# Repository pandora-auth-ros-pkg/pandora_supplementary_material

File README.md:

pandora_supplementary_material
==============================

Contains supplementary material, such as images, datasets, etc..

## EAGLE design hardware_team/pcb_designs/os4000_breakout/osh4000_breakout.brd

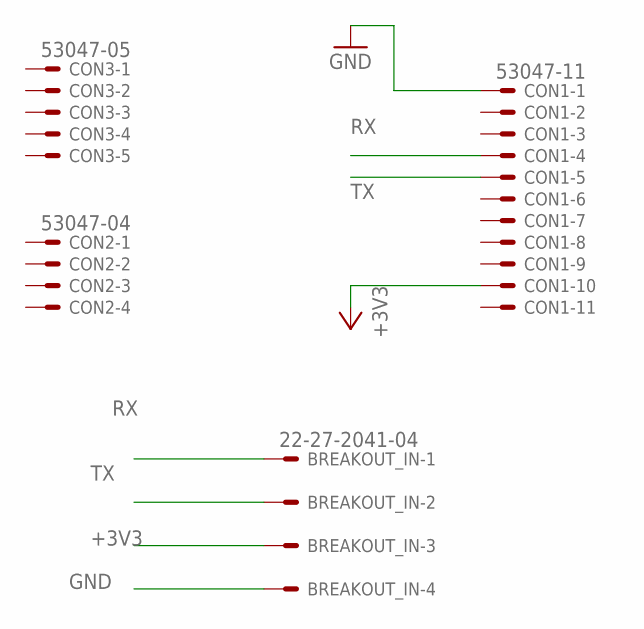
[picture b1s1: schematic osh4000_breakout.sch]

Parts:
BREAKOUT_IN: 22-27-2041-04; 6410-04
CON1: 53047-11
CON2: 53047-04
CON3: 53047-05

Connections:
+3V3: BREAKOUT_IN.3, CON1.10
GND: BREAKOUT_IN.4, CON1.1
RX: BREAKOUT_IN.1, CON1.4
TX: BREAKOUT_IN.2, CON1.5

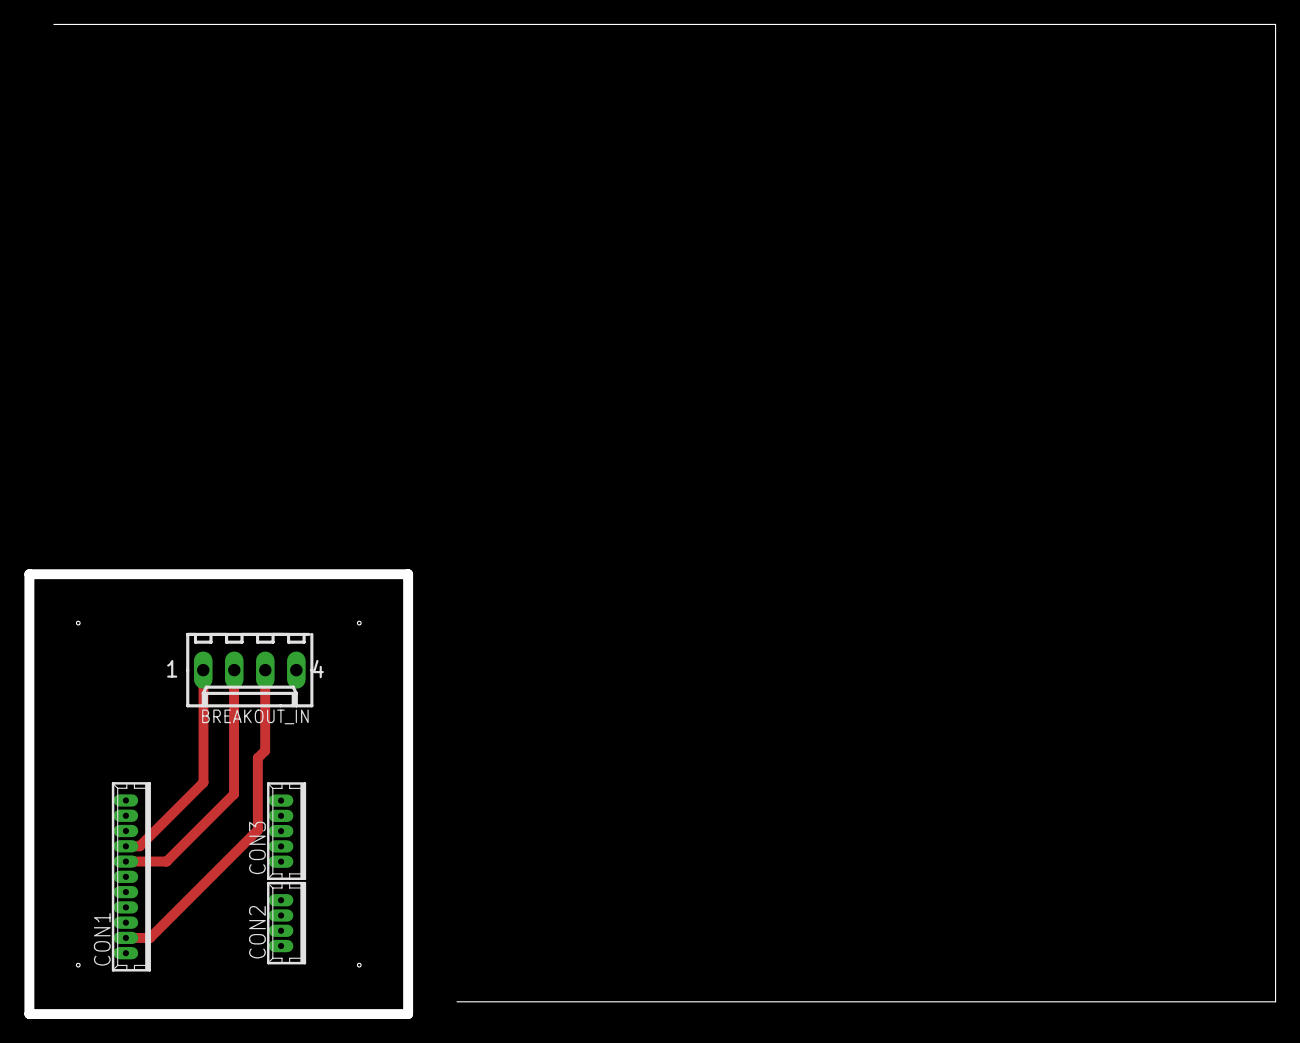
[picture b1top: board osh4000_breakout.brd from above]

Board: 2 copper layers, 31.0 x 36.0 mm, 4 parts (0 on the bottom side), 4 nets.

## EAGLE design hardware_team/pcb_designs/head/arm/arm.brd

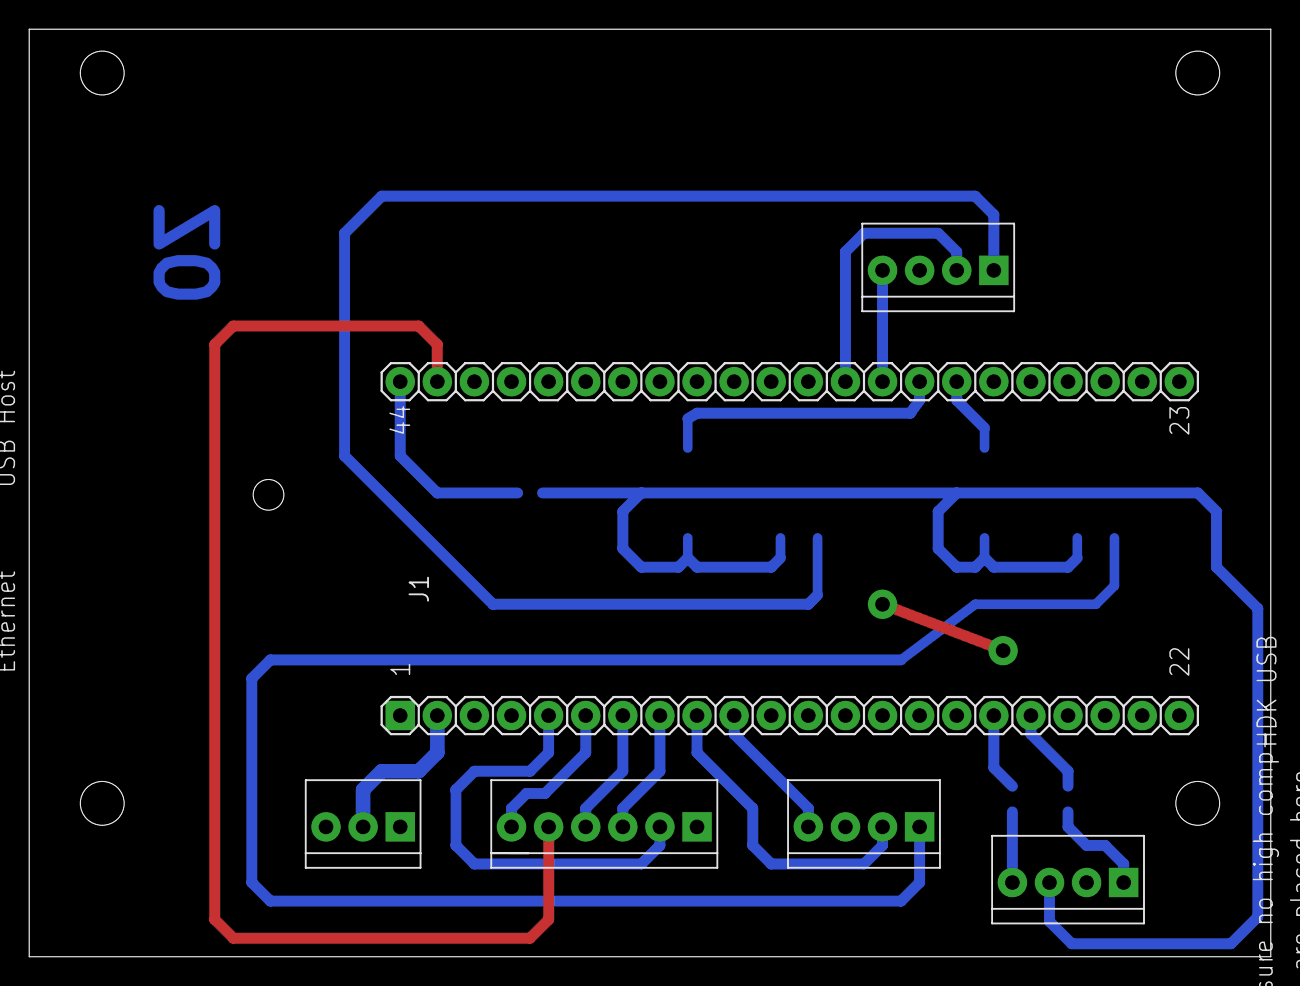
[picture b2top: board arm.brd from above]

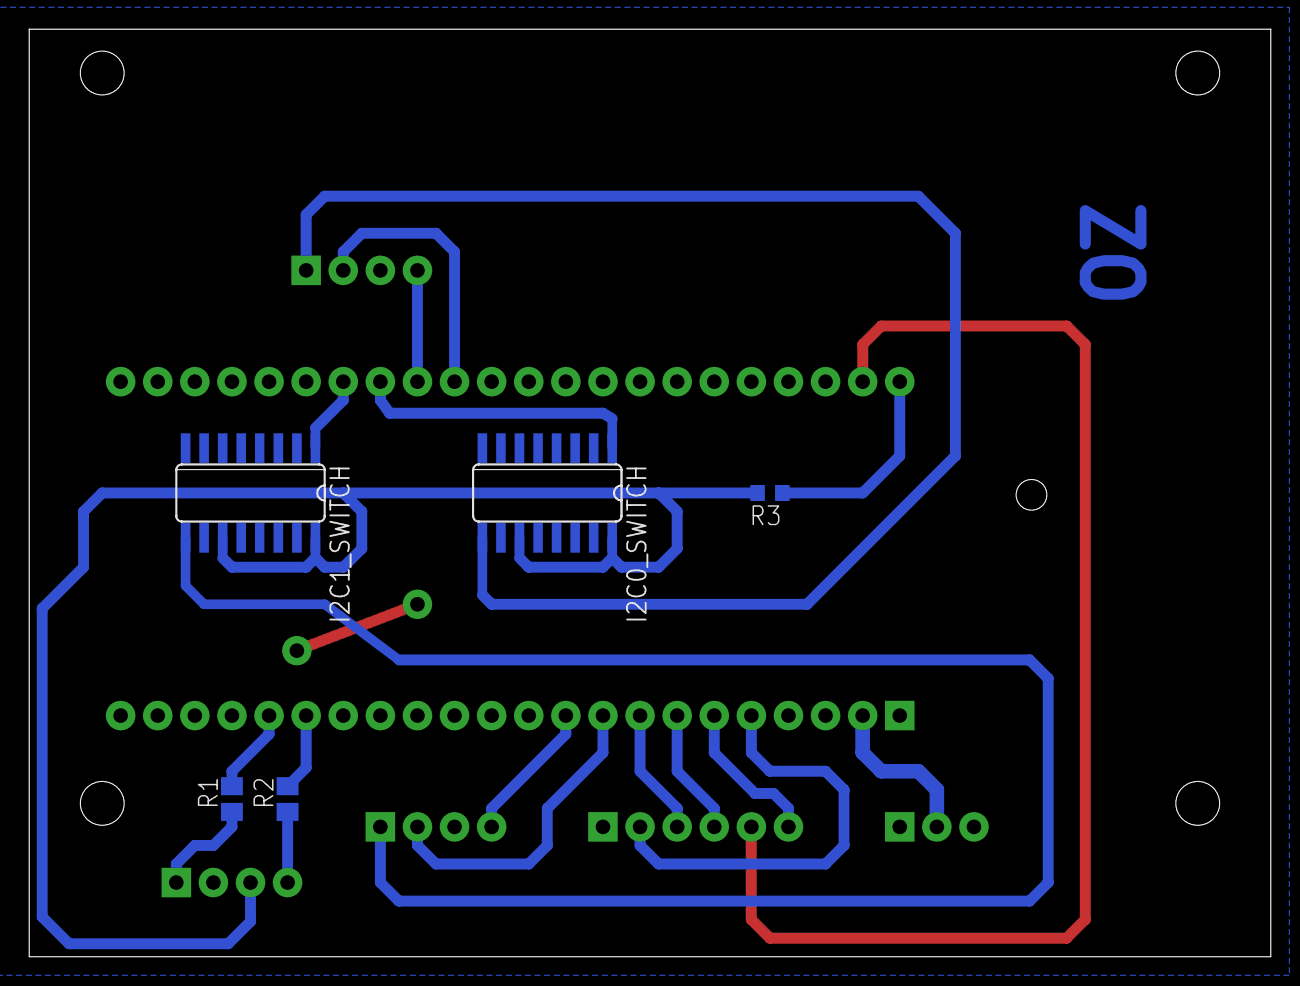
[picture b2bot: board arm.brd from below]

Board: 2 copper layers, 85.0 x 63.5 mm, 11 parts (5 on the bottom side), 21 nets.

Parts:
I2C0, I2C1: A2542WV-04P
I2C0_SWITCH, I2C1_SWITCH: MAX4674ESE+; SO16
J1: LPC4088_QUICKSTART_BOARD_REV-A
POWER: A2542WV-03P
R1, R2: 1k; R0805
R3: 1; R0603
SSP0: A2542WV-06P
UART3: A2542WV-04P

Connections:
+3V3: I2C0_SWITCH.11, I2C0_SWITCH.16, I2C1_SWITCH.11, I2C1_SWITCH.16, R3.2, UART3.3
+5V: J1.43, SSP0.5
GND: I2C0.3, I2C0_SWITCH.8, I2C0_SWITCH.10, I2C0_SWITCH.15, I2C1.3, I2C1_SWITCH.8, I2C1_SWITCH.10, I2C1_SWITCH.15, J1.1, J1.22, POWER.1, SSP0.1, UART3.2
unnamed: I2C0.1, I2C0_SWITCH.9
unnamed: J1.5, SSP0.2
unnamed: J1.8, SSP0.3
unnamed: I2C1.2, J1.9
unnamed: I2C0.2, J1.32
unnamed: I2C0.4, J1.31
unnamed: I2C1.4, J1.10
unnamed: J1.7, SSP0.4
unnamed: J1.18, R1.2
unnamed: J1.17, R2.2
unnamed: R1.1, UART3.1
unnamed: R2.1, UART3.4
unnamed: J1.2, POWER.2
unnamed: I2C1.1, I2C1_SWITCH.9
unnamed: J1.6, SSP0.6
unnamed: I2C1_SWITCH.1, J1.29
unnamed: I2C0_SWITCH.1, J1.30
unnamed: J1.44, R3.1

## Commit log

2014-03-02 add material from pandora-gitlab + vision model
2014-03-03 add att_faces, used for training the model
2014-06-03 Adds walls directory and files
    new file: vision/walls/0.png
    new file: vision/walls/1.png
    new file: vision/walls/10.png
    new file: vision/walls/11.png
    new file: vision/walls/12.png
    new file: vision/walls/13.png
2014-06-07 Added svm training first edition and renamed folder from face_training to victim_training
2014-06-19 Adds optimal filter order finder
    new file: vision/hole_detector_related/optimal_filtering_order/dataset.csv
    new file: vision/hole_detector_related/optimal_filtering_order/order.cpp
2014-06-23 Svm training by Marios
2014-06-25 Updates permutation finder
    modified: dataset.csv
    new file: dataset2.csv
    renamed: dataset.csv -> dataset_0.csv
    new file: dataset_urgent.csv
    new file: dummy.csv
    modified: order.cpp
2014-06-27 added cascade classifier
2014-11-03 Added pcb designs from Team 13-14
2014-12-30 Add blender assembly.
2015-02-07 Remove obsolete files add new images and scrips for hole
2015-02-08 Add configure script, in order to create extra_files.yaml
2015-03-05 Adds qr images.
2015-03-06 Added landoltC dataset
2015-03-12 Add Hazmat Data
2015-03-12 Update new robot assembly
2015-03-12 Add new dataset
2015-03-13 added victim trainings data version 13-14
2015-03-14 Reorganize benchmarking dataset
2015-03-15 Rename dataset images
2015-03-16 Add rgbd-thermal images for hole
2015-03-17 Update configure
    Fix relative path issue
2015-03-17 Remove wrong .swp file
2015-03-17 Add Data for the old hazmat node
2015-03-17 Update configure
    Use replace instead of strip
2015-03-20 Join dataset parts. Add image annotation
2015-03-23 Add leddar shared libraries
2015-03-24 Added epos2 shared objects
2015-03-24 Add symlinks to epos2 shared libraries
2015-03-24 Add images with 720p resolution
2015-03-26 Add point cloud bags and RGB-D images from point cloud
2015-03-26 Add annotations and benchmark parameters for dataset images
2015-03-26 Fix minor error in annotations file
2015-03-26 Added some qr images and gt for unit testing purposes
2015-03-26 Add annotations for Point Cloud images
2015-03-27 Add more specifications for the dataset images
2015-03-29 Add annotations and benchmark parameters for the ros bags containing point cloud images
2015-03-29 Modify the dataset subfolders
2015-04-06 Add training input and latest hazmat training data
2015-05-04 Add image for victim sift feature extractor test
2015-05-09 added new files necessary for victim detection
2015-05-20 Add new rgb sift classification files
2015-05-21 Add sift vocabulary file
2015-05-27 Copied x86 directory into i686. Mismatched on different architectures
2015-05-31 update training files
2015-06-28 Add frame matcher functional testing bag
2015-06-30 Remove unneccessary files for victim training and add new svm models
2015-07-12 Created directory for rl-data
2016-01-18 Epos2 symbolic links for arm architecture libs
2016-02-25 Add monstertruck blender file
2016-11-09 Add monstertruck parts
